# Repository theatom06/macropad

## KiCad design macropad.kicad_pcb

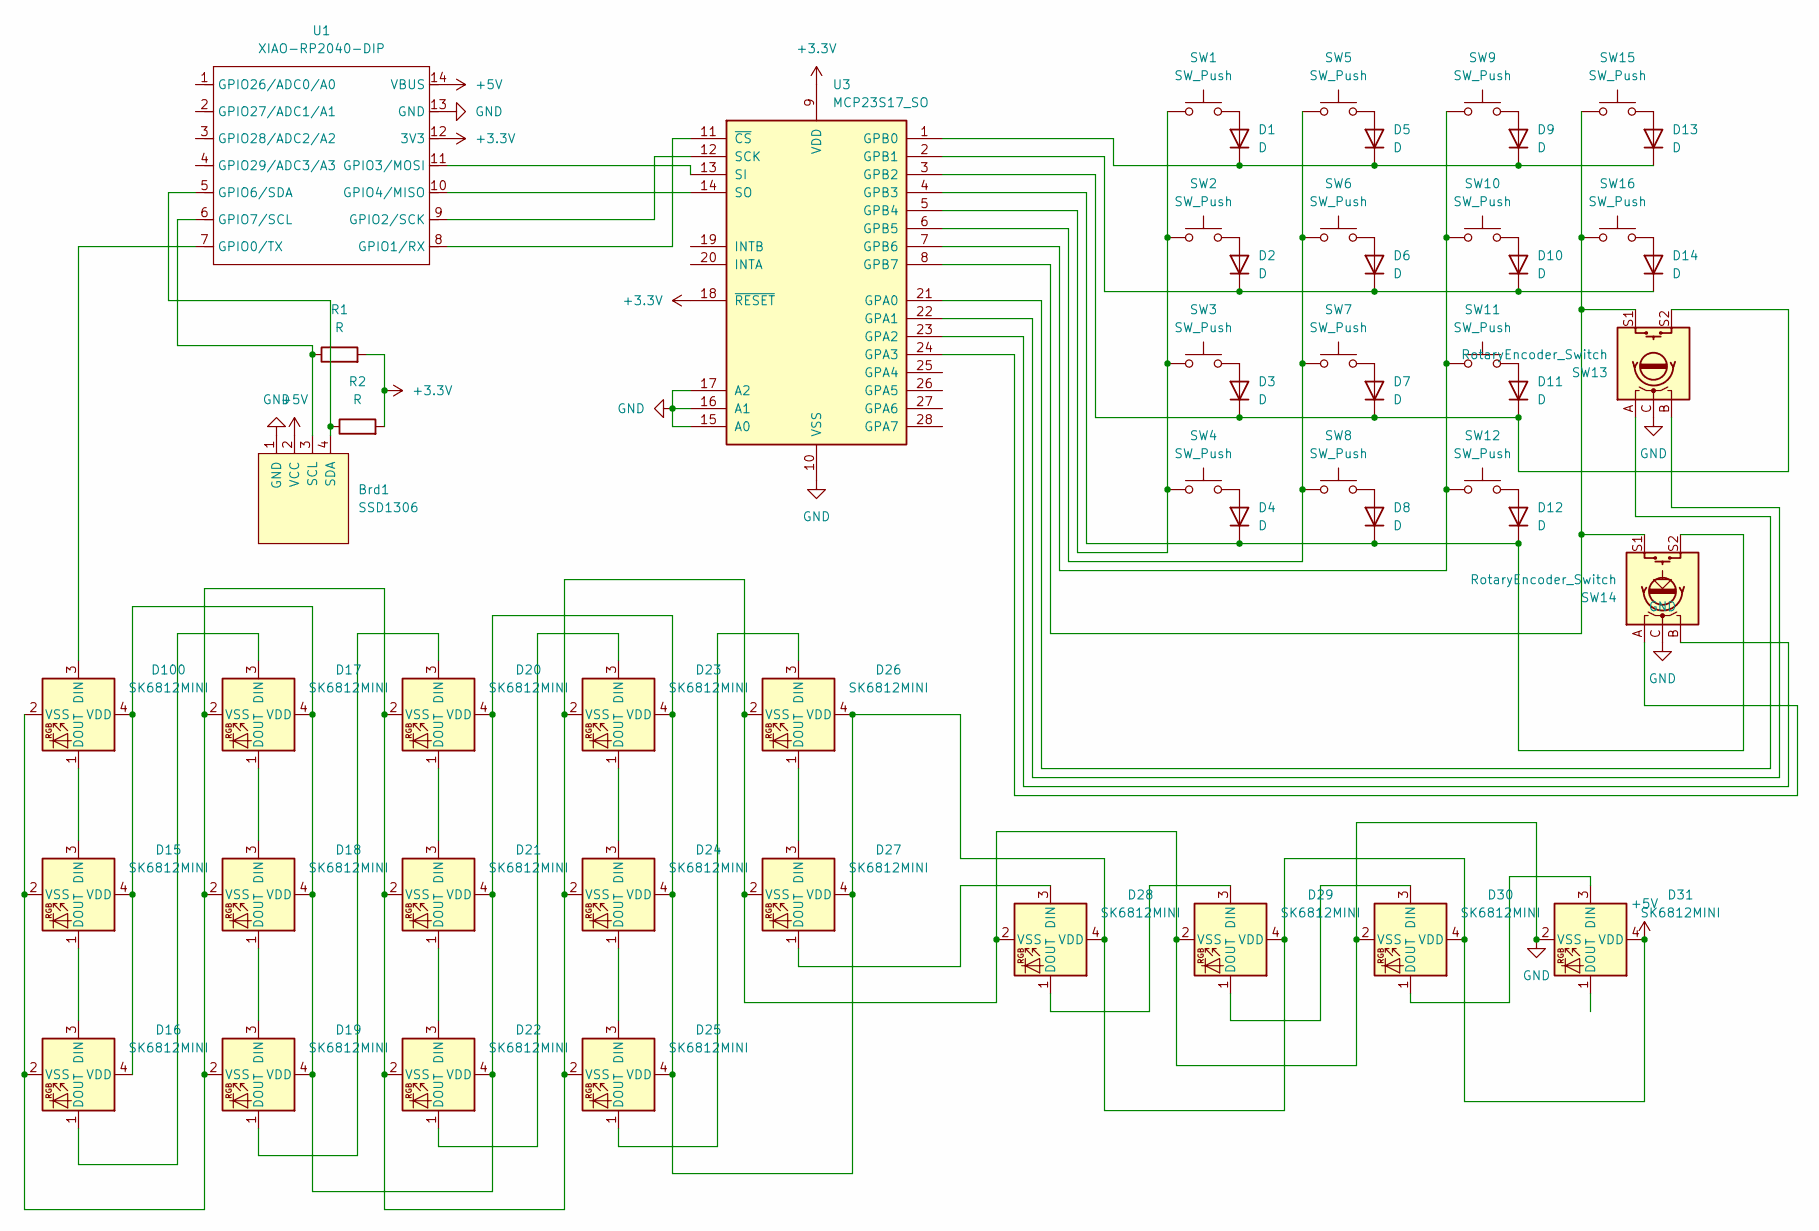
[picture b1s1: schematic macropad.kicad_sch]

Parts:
Brd1: SSD1306; 128x64OLED
D1, D2, D3, D4, D5, D6, D7, D8, D9, D10, D11, D12, D13, D14: D; D_DO-35_SOD27_P7.62mm_Horizontal
D15, D16, D17, D18, D19, D20, D21, D22, D23, D24, D25, D26, D27, D28, D29, D30, D31, D100: SK6812MINI; SK6812MINI-E
R1, R2: R; R_Axial_DIN0204_L3.6mm_D1.6mm_P7.62mm_Horizontal
SW1, SW2, SW3, SW4, SW5, SW6, SW7, SW8, SW9, SW10, SW11, SW12, SW15, SW16: SW_Push; SW_Cherry_MX_1.00u_PCB
SW13, SW14: RotaryEncoder_Switch; RotaryEncoder_Alps_EC11E-Switch_Vertical_H20mm_CircularMoun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
U1: XIAO-RP2040-DIP
U3: MCP23S17_SO; SOIC-28W_7.5x17.9mm_P1.27mm

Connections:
+3.3V: R1.2, R2.2, U1.12 (3V3), U3.9 (VDD), U3.18 (~RESET)
+5V: Brd1.2 (VCC), D15.4 (VDD), D16.4 (VDD), D17.4 (VDD), D18.4 (VDD), D19.4 (VDD), D20.4 (VDD), D21.4 (VDD), D22.4 (VDD), D23.4 (VDD), D24.4 (VDD), D25.4 (VDD), D26.4 (VDD), D27.4 (VDD), D28.4 (VDD), D29.4 (VDD), D30.4 (VDD), D31.4 (VDD), D100.4 (VDD), U1.14 (VBUS)
GND: Brd1.1 (GND), D15.2 (VSS), D16.2 (VSS), D17.2 (VSS), D18.2 (VSS), D19.2 (VSS), D20.2 (VSS), D21.2 (VSS), D22.2 (VSS), D23.2 (VSS), D24.2 (VSS), D25.2 (VSS), D26.2 (VSS), D27.2 (VSS), D28.2 (VSS), D29.2 (VSS), D30.2 (VSS), D31.2 (VSS), D100.2 (VSS), SW13.C, SW14.C, U1.13 (GND), U3.10 (VSS), U3.15 (A0), U3.16 (A1), U3.17 (A2)
unnamed: Brd1.3 (SCL), R1.1, U1.6 (GPIO7/SCL)
unnamed: Brd1.4 (SDA), R2.1, U1.5 (GPIO6/SDA)
unnamed: D1.2 (A), SW1.2
unnamed: D1.1 (K), D5.1 (K), D9.1 (K), D13.1 (K), U3.1 (GPB0)
unnamed: D2.2 (A), SW2.2
unnamed: D3.2 (A), SW3.2
unnamed: D4.2 (A), SW4.2
unnamed: D5.2 (A), SW5.2
unnamed: D6.2 (A), SW6.2
unnamed: D7.2 (A), SW7.2
unnamed: D8.2 (A), SW8.2
unnamed: D9.2 (A), SW9.2
unnamed: D10.2 (A), SW10.2
unnamed: D2.1 (K), D6.1 (K), D10.1 (K), D14.1 (K), U3.2 (GPB1)
unnamed: D11.2 (A), SW11.2
unnamed: D3.1 (K), D7.1 (K), D11.1 (K), SW13.S2, U3.3 (GPB2)
unnamed: D12.2 (A), SW12.2
unnamed: D4.1 (K), D8.1 (K), D12.1 (K), SW14.S2, U3.4 (GPB3)
unnamed: D13.2 (A), SW15.2
unnamed: D14.2 (A), SW16.2
unnamed: D15.1 (DOUT), D16.3 (DIN)
unnamed: D16.1 (DOUT), D17.3 (DIN)
unnamed: D17.1 (DOUT), D18.3 (DIN)
unnamed: D18.1 (DOUT), D19.3 (DIN)
unnamed: D19.1 (DOUT), D20.3 (DIN)
unnamed: D20.1 (DOUT), D21.3 (DIN)
unnamed: D21.1 (DOUT), D22.3 (DIN)
unnamed: D22.1 (DOUT), D23.3 (DIN)
unnamed: D23.1 (DOUT), D24.3 (DIN)
unnamed: D24.1 (DOUT), D25.3 (DIN)
unnamed: D25.1 (DOUT), D26.3 (DIN)
unnamed: D26.1 (DOUT), D27.3 (DIN)
unnamed: D27.1 (DOUT), D28.3 (DIN)
unnamed: D28.1 (DOUT), D29.3 (DIN)
unnamed: D29.1 (DOUT), D30.3 (DIN)
unnamed: D30.1 (DOUT), D31.3 (DIN)
unnamed: D100.3 (DIN), U1.7 (GPIO0/TX)
unnamed: D15.3 (DIN), D100.1 (DOUT)
unnamed: U1.8 (GPIO1/RX), U3.11 (~CS)
unnamed: U1.9 (GPIO2/SCK), U3.12 (SCK)
unnamed: U1.11 (GPIO3/MOSI), U3.13 (SI)
unnamed: U1.10 (GPIO4/MISO), U3.14 (SO)
unnamed: SW13.A, U3.21 (GPA0)
unnamed: SW13.B, U3.22 (GPA1)
unnamed: SW14.B, U3.23 (GPA2)
unnamed: SW14.A, U3.24 (GPA3)
unnamed: SW1.1, SW2.1, SW3.1, SW4.1, U3.5 (GPB4)
unnamed: SW5.1, SW6.1, SW7.1, SW8.1, U3.6 (GPB5)
unnamed: SW9.1, SW10.1, SW11.1, SW12.1, U3.7 (GPB6)
unnamed: SW13.S1, SW14.S1, SW15.1, SW16.1, U3.8 (GPB7)

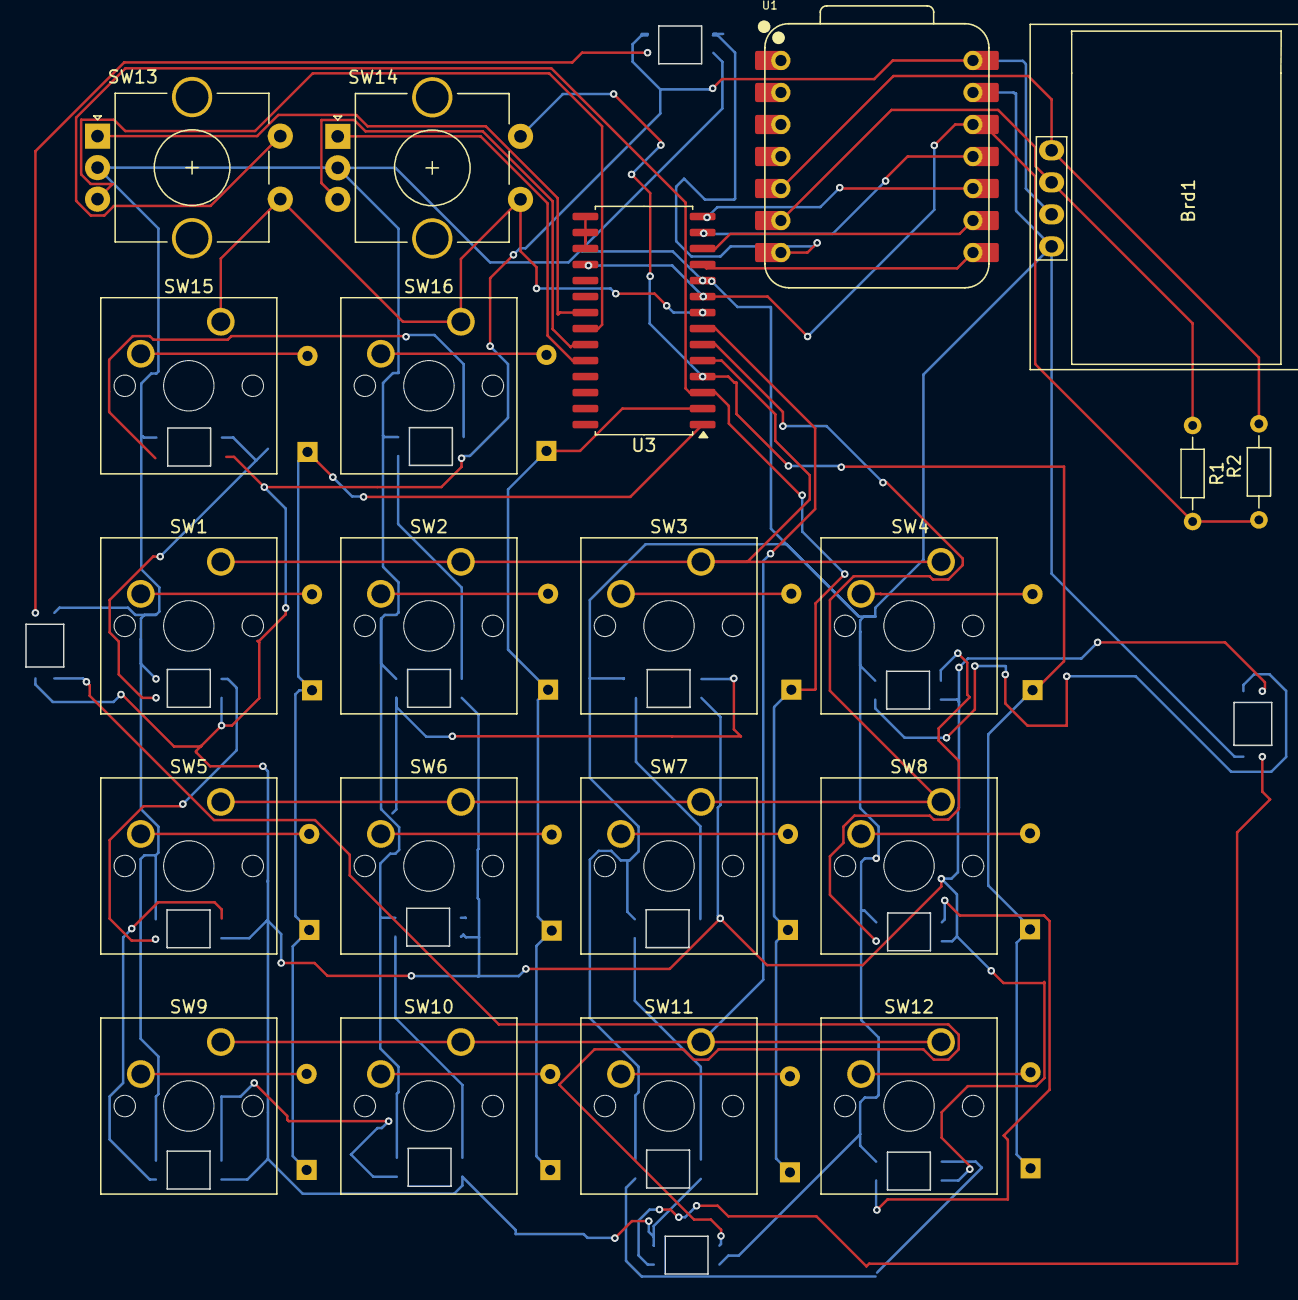
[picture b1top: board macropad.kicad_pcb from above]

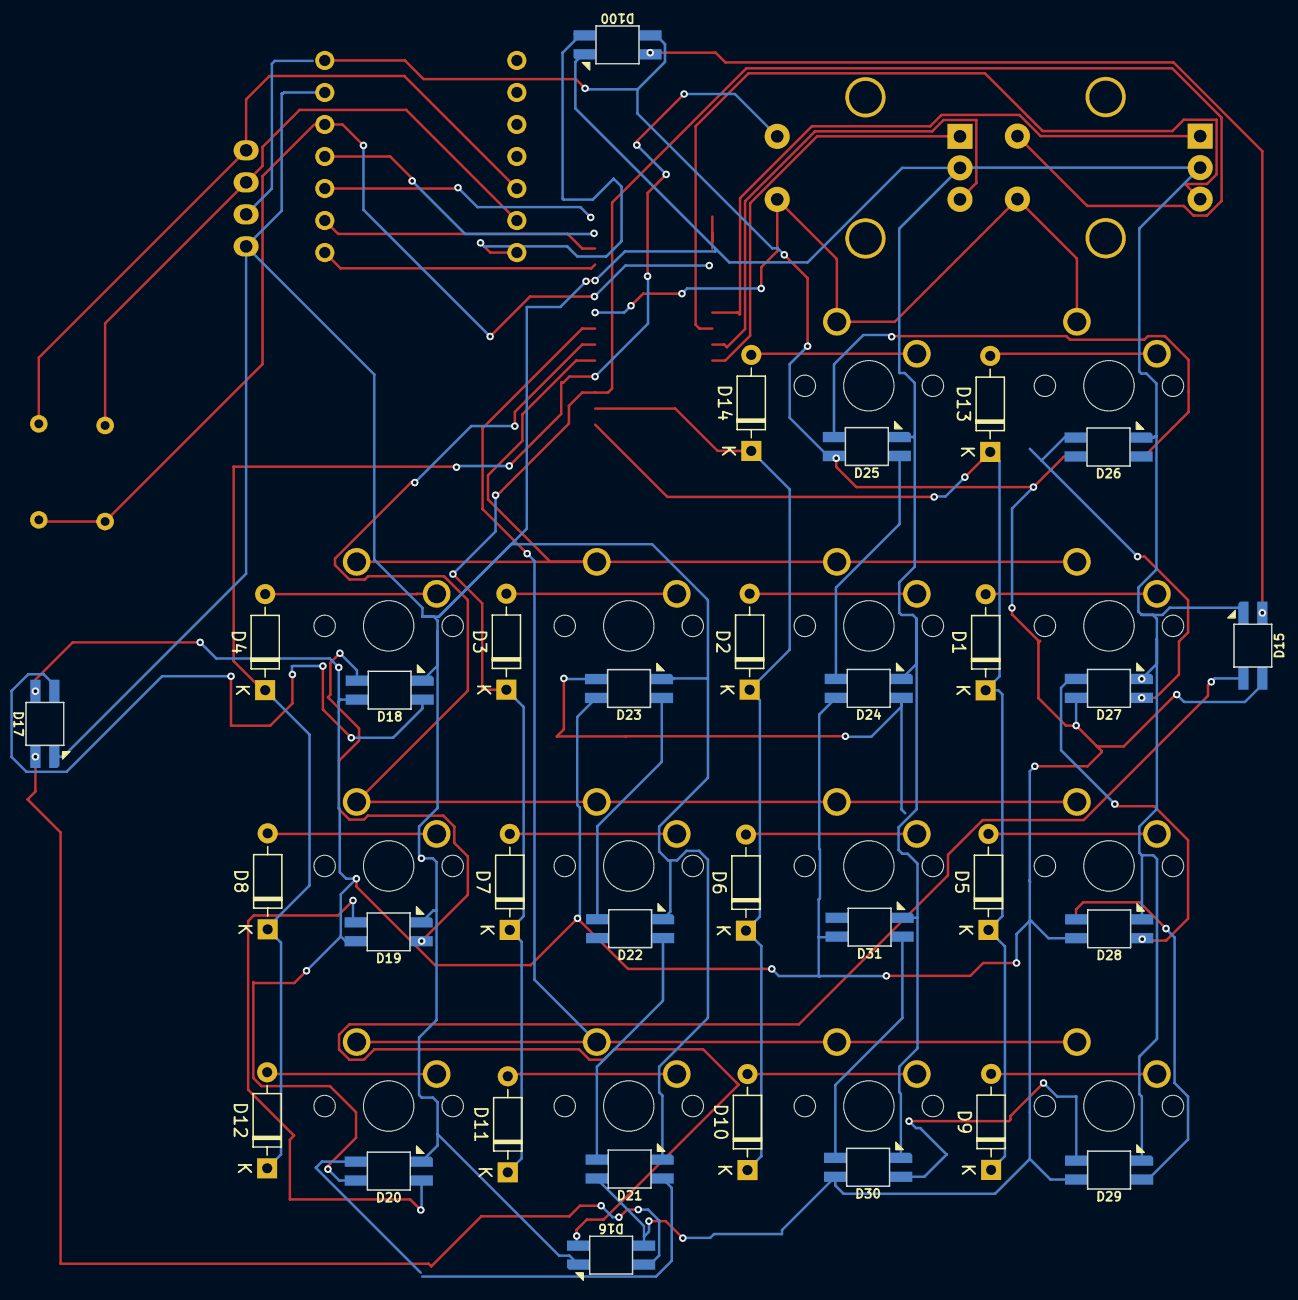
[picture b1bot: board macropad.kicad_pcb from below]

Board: 2 copper layers, 53 parts (32 on the bottom side), 53 nets.

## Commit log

2025-02-21 final
